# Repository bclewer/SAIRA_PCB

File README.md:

View this project on [CADLAB.io](https://cadlab.io/project/25017). 

# SAIRA_PCB

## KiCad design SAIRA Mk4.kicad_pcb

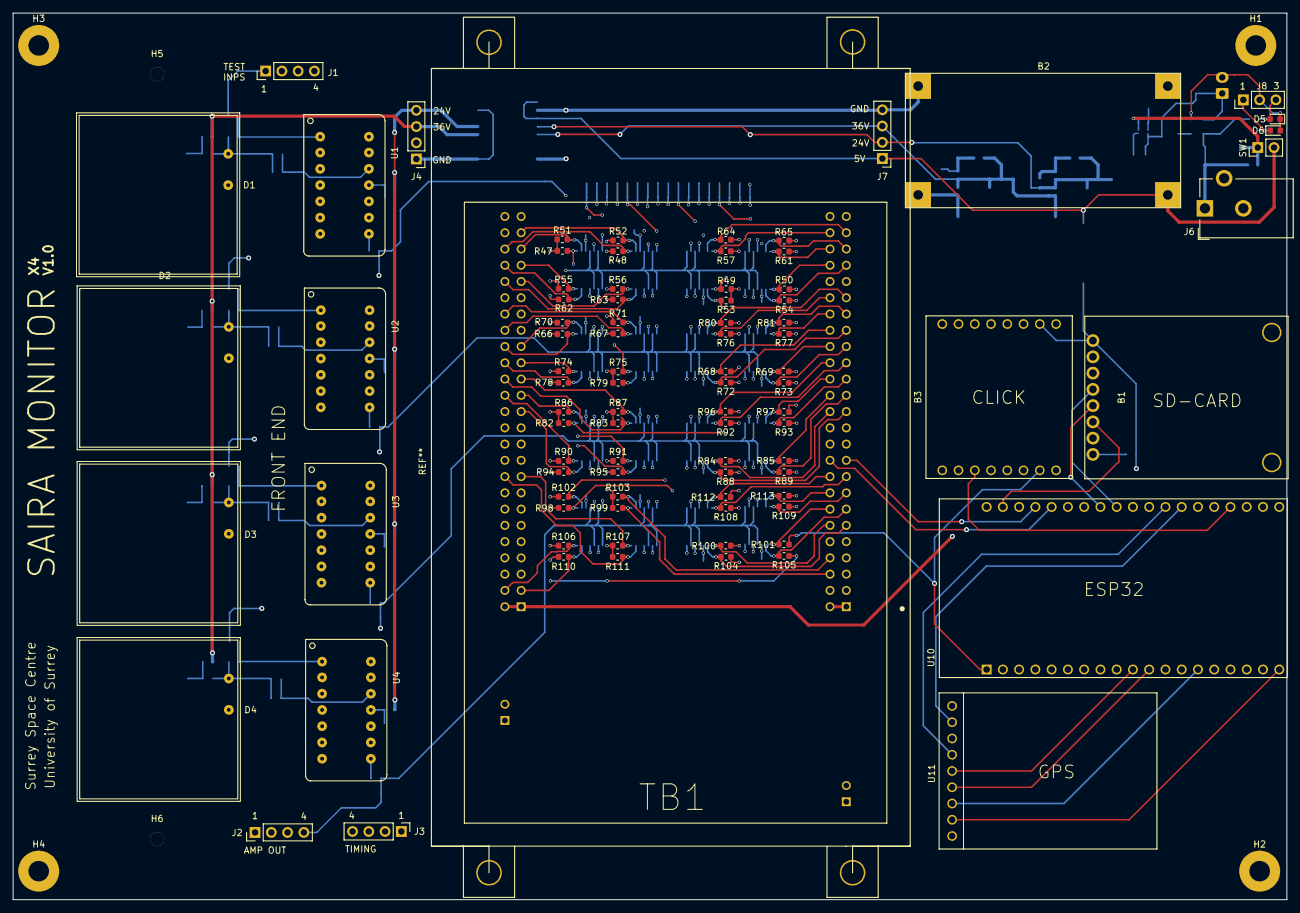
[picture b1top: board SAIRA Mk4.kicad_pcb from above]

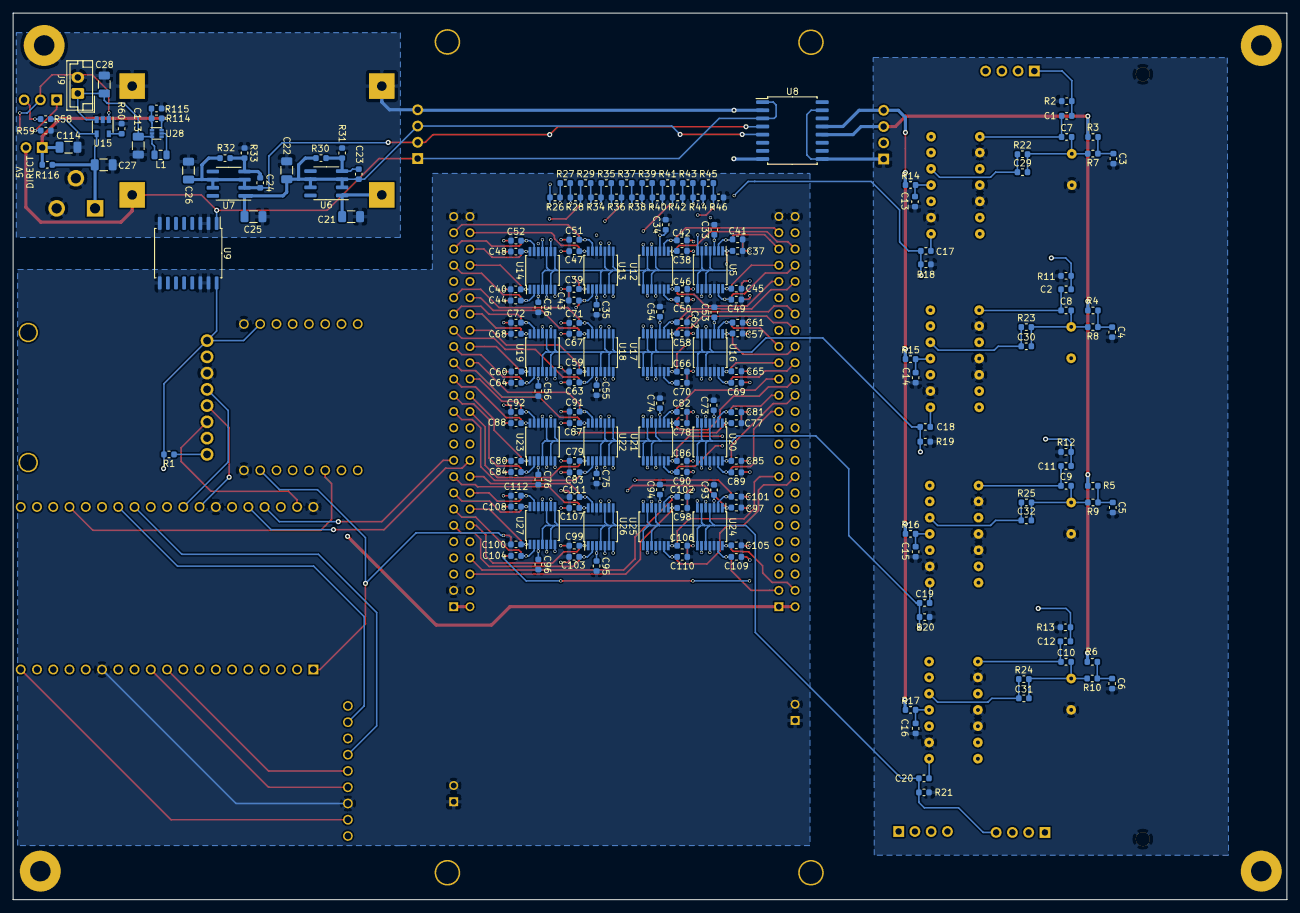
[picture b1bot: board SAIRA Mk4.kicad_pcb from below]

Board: 4 copper layers, 199.0 x 138.5 mm, 284 parts (190 on the bottom side), 150 nets.

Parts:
B1: Micro_SD_Breakout
B2: XL6009_Boost_Board
B3: Riverdi_Click
C1, C2, C11, C12: 2.2pF; C_0603_1608Metric
C3, C4, C17, C18, C19, C20, C33, C34, C35, C36, C53, C54, C55, C56, C73, C74, C75, C76, C93, C94, C95, C96: 100nF; C_0603_1608Metric
C5, C6, C7, C8, C9, C10, C23, C24, C29, C30, C31, C32: 10nF; C_0603_1608Metric
C13, C14, C15, C16: 2.2uF; C_0603_1608Metric
C21, C22, C25, C26, C27, C28, C113, C114: 10uF; C_1206_3216Metric
C37, C38, C39, C40, C41, C42, C43, C44, C45, C46, C47, C48, C49, C50, C51, C52, C57, C58, C59, C60, C61, C62, C63, C64, C65, C66, C67, C68, C69, C70, C71, C72, C77, C78, C79, C80, C81, C82, C83, C84, C85, C86, C87, C88, C89, C90, C91, C92, C97, C98, C99, C100, C101, C102, C103, C104, C105, C106, C107, C108, C109, C110, C111, C112: 4nF; C_0603_1608Metric
D1, D2, D3, D4: S3204-08
D5, D6: LED; LED_0603_1608Metric
H1: MountingHole_Pad; MountingHole_3.2mm_M3_Pad
H2, H3, H4: MountingHole; MountingHole_3.2mm_M3_Pad
H5, H6: MountingHole_Pad; MountingHole_2.2mm_M2
J1, J2, J3, J4: Conn_01x04; PinHeader_1x04_P2.54mm_Vertical
J6: Barrel_Jack_Switch_Pin3Ring; BarrelJack_CUI_PJ-102AH_Horizontal
J7: Conn_01x04_MountingPin; PinHeader_1x04_P2.54mm_Vertical
J8: Conn_01x03; PinHeader_1x03_P2.54mm_Vertical
J9: Conn_01x02; JST_EH_B2B-EH-A_1x02_P2.50mm_Vertical
L1: 1uH; L_0805_2012Metric
R1: 10K; R_0603_1608Metric
R2, R11, R12, R13: 49R9; C_0603_1608Metric
R3, R4, R5, R6: 1M; C_0603_1608Metric
R7, R8, R9, R10: 10M; C_0603_1608Metric
R14, R15, R16, R17, R22, R23, R24, R25: 100R; C_0603_1608Metric
R18, R19, R20, R21: 2K7; C_0603_1608Metric
R26, R27, R28, R29, R34, R35, R36, R37, R38, R39, R40, R41, R42, R43, R44, R45, R46: R; R_0603_1608Metric
R30, R32: 1M; R_0603_1608Metric
R31: 51K; R_0603_1608Metric
R33: 33K; R_0603_1608Metric
R47, R48, R49, R50, R51, R52, R53, R54, R55, R56, R57, R61, R62, R63, R64, R65, R66, R67, R68, R69, R70, R71, R72, R73, R74, R75, R76, R77, R78, R79, R80, R81, R82, R83, R84, R85, R86, R87, R88, R89, R90, R91, R92, R93, R94, R95, R96, R97, R98, R99, R100, R101, R102, R103, R104, R105, R106, R107, R108, R109, R110, R111, R112, R113: R_Small; R_0603_1608Metric
R58, R59: 470R; R_0603_1608Metric
R60: 2k2; R_0603_1608Metric
R114: 723k; R_0603_1608Metric
R115: 100k; R_0603_1608Metric
R116: N.M; R_0603_1608Metric
SW1: SW_DIP_x01; PinHeader_1x02_P2.54mm_Vertical
TB1: STM32F3DISCOVERY; SHIELD_STM32F3DISCOVERY
U1, U2, U3, U4: A225
U5, U12, U13, U14, U16, U17, U18, U19, U20, U21, U22, U23, U24, U25, U26, U27: LM239; TSSOP-14_4.4x5mm_P0.65mm
U6, U7: LM317L_SO8; SOIC-8_3.9x4.9mm_P1.27mm
U8, U9: ISO7840; SOIC-16W_7.5x10.3mm_P1.27mm
U10: ESP32-DEVKITC-32D; MODULE_ESP32-DEVKITC-32D
U11: Adafruit_Ult_GPS
U15: MCP73811T; SOT-23-5
U28: TPS61023; SOT-563

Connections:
3V3: B3.7, R47.1, R48.1, R49.1, R50.1, R51.1, R52.1, R53.1, R54.1, R55.1, R56.1, R57.1, R61.1, R62.1, R63.1, R64.1, R65.1, R66.1, R67.1, R68.1, R69.1, R70.1, R71.1, R72.1, R73.1, R74.1, R75.1, R76.1, R77.1, R78.1, R79.1, R80.1, R81.1, R82.1, R83.1, R84.1, R85.1, R86.1, R87.1, R88.1, R89.1, R90.1, R91.1, R92.1, R93.1, R94.1, R95.1, R96.1, R97.1, R98.1, R99.1, R100.1, R101.1, R102.1, R103.1, R104.1, R105.1, R106.1, R107.1, R108.1, R109.1, R110.1, R111.1, R112.1, R113.1, U10.1
5V: B1.1, B3.10, R1.2, TB1.51, TB1.52, U9.16, U10.19, U11.8
24V: C24.1, C26.1, C33.1, C34.1, C35.1, C36.1, C53.1, C54.1, C55.1, C56.1, C73.1, C74.1, C75.1, C76.1, C93.1, C94.1, C95.1, C96.1, J7.2, R26.1, R32.2, U5.3, U7.2, U7.3, U7.6, U7.7, U8.4, U12.3, U13.3, U14.3, U16.3, U17.3, U18.3, U19.3, U20.3, U21.3, U22.3, U23.3, U24.3, U25.3, U26.3, U27.3
24V_A: J4.4, R14.1, R15.1, R16.1, R17.1, U8.13
35V_BOOST: B2.3, C21.1, U6.1
36V: C22.1, C23.1, C25.1, J7.3, R30.2, U6.2, U6.3, U6.6, U6.7, U7.1, U8.5
36V_A: J4.3, R3.2, R4.2, R5.2, R6.2, U8.12
/Front End/P1_OUT: C1.1, C7.1, U1.1
/Front End/P2_OUT: C2.1, C8.1, U2.1
/Front End/P3_OUT: C9.1, C11.1, U3.1
/Front End/P4_OUT: C10.1, C12.1, U4.1
A1_OUT: C17.1, J2.1, R18.1, U5.4, U5.6, U5.8, U5.10, U12.4, U12.6, U12.8, U12.10, U13.4, U13.6, U13.8, U13.10, U14.4, U14.6, U14.8, U14.10
A1_TIM: C29.1, J3.1, R22.1, U1.12
A2_OUT: C18.1, J2.2, R19.1, U16.4, U16.6, U16.8, U16.10, U17.4, U17.6, U17.8, U17.10, U18.4, U18.6, U18.8, U18.10, U19.4, U19.6, U19.8, U19.10
A2_TIM: C30.1, J3.2, R23.1, U2.12
A3_OUT: C19.1, J2.3, R20.1, U20.4, U20.6, U20.8, U20.10, U21.4, U21.6, U21.8, U21.10, U22.4, U22.6, U22.8, U22.10, U23.4, U23.6, U23.8, U23.10
A3_TIM: C32.1, J3.3, R25.1, U3.12
A4_OUT: C20.1, J2.4, R21.1, U24.4, U24.6, U24.8, U24.10, U25.4, U25.6, U25.8, U25.10, U26.4, U26.6, U26.8, U26.10, U27.4, U27.6, U27.8, U27.10
A4_TIM: C31.1, J3.4, R24.1, U4.12
BAT_IN: C28.1, C113.1, J9.1, L1.1, U15.3, U28.2, U28.3
D1_CHL_0: C37.2, R47.2, TB1.22, U5.1
D1_CHL_1: C41.2, R51.2, TB1.95, U5.2
D1_CHL_2: C45.2, R55.2, TB1.93, U5.14
D1_CHL_3: C49.2, R62.2, TB1.94, U5.13
D1_CHL_4: C38.2, R48.2, TB1.96, U12.1
D1_CHL_5: C42.2, R52.2, TB1.97, U12.2
D1_CHL_6: C46.2, R56.2, TB1.91, U12.14
D1_CHL_7: C50.2, R63.2, TB1.92, U12.13
D1_CHL_8: C39.2, R49.2, TB1.42, U13.1
D1_CHL_9: C43.2, R53.2, TB1.41, U13.2
D1_CHL_10: C47.2, R57.2, TB1.48, U13.14
D1_CHL_11: C51.2, R64.2, TB1.47, U13.13
D1_CHL_12: C40.2, R50.2, TB1.44, U14.1
D1_CHL_13: C44.2, R54.2, TB1.43, U14.2
D1_CHL_14: C48.2, R61.2, TB1.46, U14.14
D1_CHL_15: C52.2, R65.2, TB1.45, U14.13
D2_CHL_0: C57.2, R66.2, TB1.84, U16.1
D2_CHL_1: C61.2, R70.2, TB1.83, U16.2
D2_CHL_2: C65.2, R74.2, TB1.81, U16.14
D2_CHL_3: C69.2, R78.2, TB1.82, U16.13
D2_CHL_4: C58.2, R67.2, TB1.86, U17.1
D2_CHL_5: C62.2, R71.2, TB1.88, U17.2
D2_CHL_6: C66.2, R75.2, TB1.89, U17.14
D2_CHL_7: C70.2, R79.2, TB1.90, U17.13
D2_CHL_8: C59.2, R68.2, TB1.36, U18.1
D2_CHL_9: C63.2, R72.2, TB1.35, U18.2
D2_CHL_10: C67.2, R76.2, TB1.40, U18.14
D2_CHL_11: C71.2, R80.2, TB1.39, U18.13
D2_CHL_12: C60.2, R69.2, TB1.34, U19.1
D2_CHL_13: C64.2, R73.2, TB1.33, U19.2
D2_CHL_14: C68.2, R77.2, TB1.38, U19.14
D2_CHL_15: C72.2, R81.2, TB1.37, U19.13
D3_CHL_0: C77.2, R82.2, TB1.24, U20.1
D3_CHL_1: C81.2, R86.2, TB1.77, U20.2
D3_CHL_2: C85.2, R90.2, TB1.78, U20.14
D3_CHL_3: C89.2, R94.2, TB1.75, U20.13
D3_CHL_4: C78.2, R83.2, TB1.80, U21.1
D3_CHL_5: C82.2, R87.2, TB1.79, U21.2
D3_CHL_6: C86.2, R91.2, TB1.73, U21.14
D3_CHL_7: C90.2, R95.2, TB1.74, U21.13
D3_CHL_8: C79.2, R84.2, TB1.26, U22.1
D3_CHL_9: C83.2, R88.2, TB1.25, U22.2
D3_CHL_10: C87.2, R92.2, TB1.31, U22.14
D3_CHL_11: C91.2, R96.2, TB1.32, U22.13
D3_CHL_12: C80.2, R85.2, TB1.28, U23.1
D3_CHL_13: C84.2, R89.2, TB1.27, U23.2
D3_CHL_14: C88.2, R93.2, TB1.29, U23.14
D3_CHL_15: C92.2, R97.2, TB1.30, U23.13
D4_CHL_0: C97.2, R98.2, TB1.7, U24.1
D4_CHL_1: C101.2, R102.2, TB1.5, U24.2
D4_CHL_2: C105.2, R106.2, TB1.54, U24.14
D4_CHL_3: C109.2, R110.2, TB1.53, U24.13
D4_CHL_4: C98.2, R99.2, TB1.6, U25.1
D4_CHL_5: C102.2, R103.2, TB1.8, U25.2
D4_CHL_6: C106.2, R107.2, TB1.67, U25.14
D4_CHL_7: C110.2, R111.2, TB1.68, U25.13
D4_CHL_8: C99.2, R100.2, TB1.12, U26.1
D4_CHL_9: C103.2, R104.2, TB1.11, U26.2
D4_CHL_10: C107.2, R108.2, TB1.17, U26.14
D4_CHL_11: C111.2, R112.2, TB1.18, U26.13
D4_CHL_12: C100.2, R101.2, TB1.14, U27.1
D4_CHL_13: C104.2, R105.2, TB1.13, U27.2
D4_CHL_14: C108.2, R109.2, TB1.15, U27.14
D4_CHL_15: C112.2, R113.2, TB1.16, U27.13
DC_DIRECT: C114.1, R114.2, R116.2, SW1.1, U28.6
GNDA: C3.2, C4.2, C5.2, C6.2, C13.2, C14.2, C15.2, C16.2, D1.1, D3.1, D4.1, H5.1, H6.1, J4.1, R2.2, R11.2, R12.2, R13.2, R18.2, R19.2, R20.2, R21.2, U1.2, U1.4, U1.5, U1.9, U2.2, U2.4, U2.5, U2.9, U3.2, U3.4, U3.5, U3.9, U4.2, U4.4, U4.5, U4.9, U8.9, U8.15
GNDD: B1.3, B3.8, B3.9, C33.2, C34.2, C35.2, C36.2, C37.1, C38.1, C39.1, C40.1, C41.1, C42.1, C43.1, C44.1, C45.1, C46.1, C47.1, C48.1, C49.1, C50.1, C51.1, C52.1, C53.2, C54.2, C55.2, C56.2, C57.1, C58.1, C59.1, C60.1, C61.1, C62.1, C63.1, C64.1, C65.1, C66.1, C67.1, C68.1, C69.1, C70.1, C71.1, C72.1, C73.2, C74.2, C75.2, C76.2, C77.1, C78.1, C79.1, C80.1, C81.1, C82.1, C83.1, C84.1, C85.1, C86.1, C87.1, C88.1, C89.1, C90.1, C91.1, C92.1, C93.2, C94.2, C95.2, C96.2, C97.1, C98.1, C99.1, C100.1, C101.1, C102.1, C103.1, C104.1, C105.1, C106.1, C107.1, C108.1, C109.1, C110.1, C111.1, C112.1, R46.2, TB1.3, TB1.49, TB1.50, TB1.99, TB1.100, TB1.101, TB1.102, TB1.103, TB1.104, U5.12, U9.9, U9.14, U9.15, U10.14, U10.20, U10.26, U11.7, U12.12, U13.12, U14.12, U16.12, U17.12, U18.12, U19.12, U20.12, U21.12, U22.12, U23.12, U24.12, U25.12, U26.12, U27.12
GNDREF: B2.2, B2.4, C21.2, C22.2, C25.2, C26.2, C27.1, C28.2, C113.2, C114.2, H1.1, J6.2, J6.3, J7.4, J9.2, R31.1, R33.1, R59.1, R60.1, R115.1, U8.2, U8.8, U9.2, U9.3, U9.8, U15.2, U28.4
GPS_EN: U10.32, U11.2
GPS_FIX: U10.31, U11.4
HSPI_CLK: B3.4, U10.12
HSPI_IN: B3.5, U10.13
HSPI_OUT: B3.6, U10.15
LEVEL0: R45.2, R46.1, U5.7, U16.7, U20.7, U24.7
LEVEL1: R44.2, R45.1, U5.5, U16.5, U20.5, U24.5
LEVEL2: R43.2, R44.1, U5.9, U16.9, U20.9, U24.9
LEVEL3: R42.2, R43.1, U5.11, U16.11, U20.11, U24.11
LEVEL4: R41.2, R42.1, U12.7, U17.7, U21.7, U25.7
LEVEL5: R40.2, R41.1, U12.5, U17.5, U21.5, U25.5
LEVEL6: R39.2, R40.1, U12.9, U17.9, U21.9, U25.9
LEVEL7: R38.2, R39.1, U12.11, U17.11, U21.11, U25.11
LEVEL8: R37.2, R38.1, U13.7, U18.7, U22.7, U26.7
LEVEL9: R36.2, R37.1, U13.5, U18.5, U22.5, U26.5
LEVEL10: R35.2, R36.1, U13.9, U18.9, U22.9, U26.9
LEVEL11: R34.2, R35.1, U13.11, U18.11, U22.11, U26.11
LEVEL12: R29.2, R34.1, U14.7, U19.7, U23.7, U27.7
LEVEL13: R28.2, R29.1, U14.5, U19.5, U23.5, U27.5
LEVEL14: R27.2, R28.1, U14.9, U19.9, U23.9, U27.9
LEVEL15: R26.2, R27.1, U14.11, U19.11, U23.11, U27.11
unnamed: B1.8, R1.1
unnamed: C1.2, J1.1, R2.1
unnamed: C2.2, J1.2, R11.1
unnamed: C3.1, R3.1, R7.1
unnamed: C4.1, R4.1, R8.1
unnamed: C5.1, R5.1, R9.1
unnamed: C6.1, R6.1, R10.1
unnamed: C10.2, C31.2, D4.2, R10.2, R24.2
unnamed: C11.2, J1.3, R12.1
unnamed: C12.2, J1.4, R13.1
unnamed: C13.1, R14.2, U1.11
unnamed: C14.1, R15.2, U2.11
unnamed: C15.1, R16.2, U3.11
unnamed: C16.1, R17.2, U4.11
unnamed: C17.2, U1.8
unnamed: C18.2, U2.8
unnamed: C19.2, U3.8
unnamed: C20.2, U4.8
unnamed: C23.2, R30.1, R31.2, U6.4
unnamed: C24.2, R32.1, R33.2, U7.4
unnamed: C27.2, J6.1, R58.2, R116.1, U15.4
unnamed: C7.2, C29.2, D1.2, R7.2, R22.2
unnamed: C8.2, C30.2, D2.2, R8.2, R23.2
unnamed: C9.2, C32.2, D3.2, R9.2, R25.2
unnamed: D5.1, D6.2, J8.2, U15.1
unnamed: D5.2, J8.3, R58.1
unnamed: D6.1, J8.1, R59.2
unnamed: L1.2, U28.5
unnamed: R60.2, U15.5
unnamed: R114.1, R115.2, U28.1
unnamed: TB1.1, TB1.2
PSU_5V_IN: B2.1, J7.1, SW1.2, U8.1, U8.3, U9.1
SD_CS: B1.7, U10.29
TFT_CS: B3.3, U10.35
UART0_RX: TB1.20, U10.24
UART0_TX: TB1.19, U10.23
UART1_RX: U10.10, U11.5
UART1_TX: U10.11, U11.6
VSPI_CLK: B1.4, U10.28
VSPI_IN: B1.5, U10.27
VSPI_OUT: B1.6, U10.21

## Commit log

2021-12-17 Backlink to CADLAB.io has been added.
